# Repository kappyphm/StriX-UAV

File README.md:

# Small Fixed-Wing UAV Project

## Overview
This repository contains the design, control circuitry, firmware, and hardware assembly instructions for a small fixed-wing Unmanned Aerial Vehicle (UAV). The UAV supports remote control operation with a range of 500m–1km, automatic stabilization, GPS-based autonomous flight, and a return-to-home feature upon signal loss. The system is built around the STM32F103C8T6 microcontroller.

## Features
- **Remote Control**: 6 analog channels and 2 digital channels for precise control via an NRF24L01 module.
- **Flight Controller (FC)**:
  - Decodes control signals from NRF24L01 to manage 2 aileron servos, 1 rudder servo, 1 elevator servo, and 1 brushless motor ESC.
  - Reads UART signals from a GPS module for autonomous flight and return-to-home functionality.
  - Uses I2C IMU (ICM20948) for flight stabilization.
  - Supports firmware flashing and debugging via SWD.
  - Compatible with 2S–3S LiPo batteries, ensuring stable power delivery.
- **Flight Capabilities**:
  - Remote control with effective range of 500m–1km.
  - Automatic stabilization for smooth flight.
  - Autonomous flight via preloaded GPS waypoints.
  - Return-to-home feature on signal loss.

## Hardware Components
### Transmitter (TX) PCB
- **Function**: Captures 6 analog and 2 digital channels from user input.
- **Communication**: Transmits control signals via NRF24L01 module.

### Flight Controller (FC)
- **Microcontroller**: STM32F103C8T6.
- **Function**: Receives 6 PWM and 2 digital channels via NRF24L01.
- **Peripherals**:
  - 2 aileron servos, 1 rudder servo, 1 elevator servo.
  - 1 ESC for brushless motor control.
  - GPS module (UART) for navigation.
  - ICM20948 IMU (I2C) for stabilization.
- **Power**: Supports 2S–3S LiPo batteries with stable power regulation.
- **Debugging**: SWD interface for firmware updates and debugging.

## Contributing
Contributions are welcome! Please follow these steps:
1. Fork the repository.
2. Create a new branch (`git checkout -b feature/your-feature`).
3. Commit your changes (`git commit -m "Add your feature"`).
4. Push to the branch (`git push origin feature/your-feature`).
5. Open a pull request.

## License
This project is licensed under the MIT License. See the `LICENSE` file for details.

## Contact
For questions or suggestions, open an issue or contact [your email or GitHub handle].

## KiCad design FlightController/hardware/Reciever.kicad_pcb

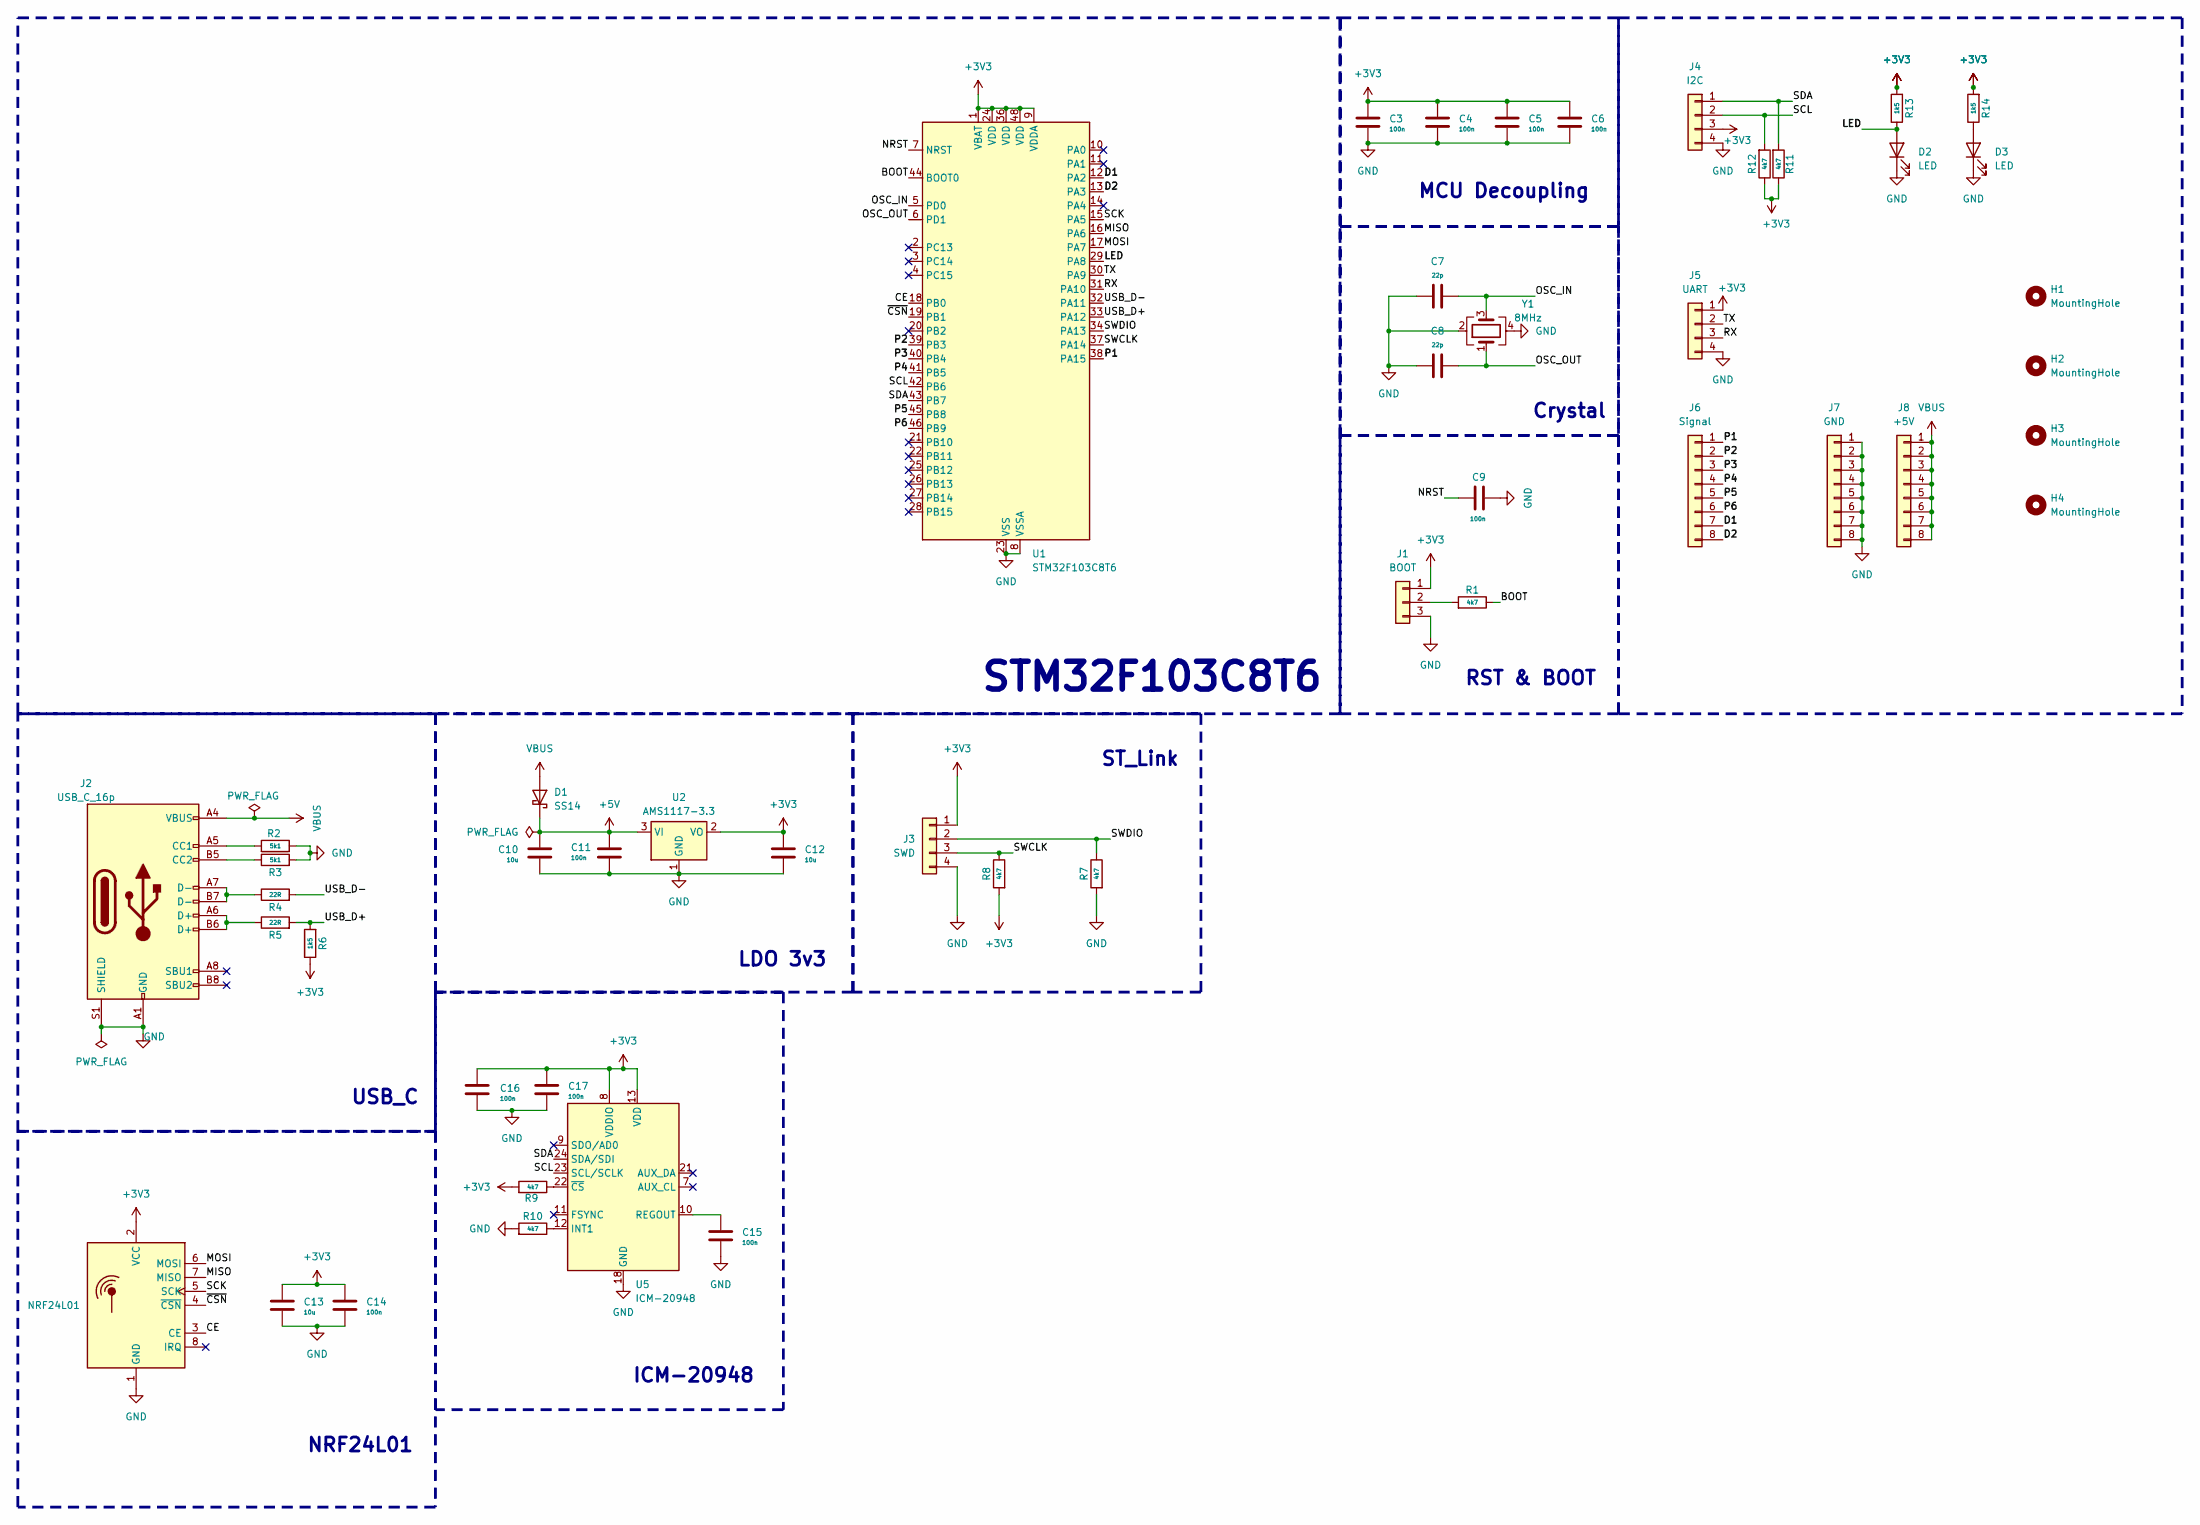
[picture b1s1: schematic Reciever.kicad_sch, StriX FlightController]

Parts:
C3, C4, C5, C6, C9, C11, C14, C15, C16, C17: 100n; C_0603_1608Metric
C7, C8: 22p; C_0603_1608Metric
C10, C12, C13: 10u; C_0603_1608Metric
D1: SS14; D_SMA
D2, D3: LED; LED_1206_3216Metric
H1, H2, H3, H4: MountingHole; MountingHole_2.5mm
J1: BOOT; PinHeader_1x03_P2.54mm_Vertical
J2: USB_C_16p; USB_C_Receptacle_HRO_TYPE-C-31-M-12
J3: SWD; PinHeader_1x04_P2.54mm_Vertical
J4: I2C; PinHeader_1x04_P2.54mm_Vertical
J5: UART; PinHeader_1x04_P2.54mm_Vertical
J6: Signal; PinHeader_1x08_P2.54mm_Vertical
J7: GND; PinHeader_1x08_P2.54mm_Vertical
J8: +5V; PinHeader_1x08_P2.54mm_Vertical
R1, R7, R8, R9, R10, R11, R12: 4k7; R_0603_1608Metric
R2, R3: 5k1; R_0603_1608Metric
R4, R5: 22R; R_0603_1608Metric
R6, R13, R14: 1k5; R_0603_1608Metric
U1: STM32F103C8T6; LQFP-48_7x7mm_P0.5mm
U2: AMS1117-3.3; SOT-223-3_TabPin2
U4: NRF24L01; NRF24L01_PA_LNA
U5: ICM-20948; InvenSense_QFN-24_3x3mm_P0.4mm
Y1: 8MHz; Crystal_SMD_5032-4Pin_5.0x3.2mm

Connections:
+3V3: C3.1, C4.1, C5.1, C6.1, C12.1, C13.1, C14.1, C16.1, C17.1, J1.1, J3.1, J4.3, J5.1, R6.1, R8.2, R9.2, R11.1, R12.1, R13.2, R14.2, U1.1 (VBAT), U1.9 (VDDA), U1.24 (VDD), U1.36 (VDD), U1.48 (VDD), U2.2 (VO), U4.2 (VCC), U5.8 (VDDIO), U5.13 (VDD)
+5V: C10.1, C11.1, D1.1 (K), U2.3 (VI)
/BOOT: R1.1, U1.44 (BOOT0)
/CE: U1.18 (PB0), U4.3 (CE)
/D1: J6.7, U1.12 (PA2)
/D2: J6.8, U1.13 (PA3)
/LED: D2.2 (A), R13.1, U1.29 (PA8)
/MISO: U1.16 (PA6), U4.7 (MISO)
/MOSI: U1.17 (PA7), U4.6 (MOSI)
/NRST: C9.1, U1.7 (NRST)
/OSC_IN: C7.2, U1.5 (PD0), Y1.3
/OSC_OUT: C8.2, U1.6 (PD1), Y1.1
/P1: J6.1, U1.38 (PA15)
/P2: J6.2, U1.39 (PB3)
/P3: J6.3, U1.40 (PB4)
/P4: J6.4, U1.41 (PB5)
/P5: J6.5, U1.45 (PB8)
/P6: J6.6, U1.46 (PB9)
/RX: J5.3, U1.31 (PA10)
/SCK: U1.15 (PA5), U4.5 (SCK)
/SCL: J4.2, R12.2, U1.42 (PB6), U5.23 (SCL/SCLK)
/SDA: J4.1, R11.2, U1.43 (PB7), U5.24 (SDA/SDI)
/SWCLK: J3.3, R8.1, U1.37 (PA14)
/SWDIO: J3.2, R7.1, U1.34 (PA13)
/TX: J5.2, U1.30 (PA9)
/USB_D+: R5.2, R6.2, U1.33 (PA12)
/USB_D-: R4.2, U1.32 (PA11)
/~CSN: U1.19 (PB1), U4.4 (~CSN)
GND: C3.2, C4.2, C5.2, C6.2, C7.1, C8.1, C9.2, C10.2, C11.2, C12.2, C13.2, C14.2, C15.2, C16.2, C17.2, D2.1 (K), D3.1 (K), J1.3, J2.A1 (GND), J2.A12 (GND), J2.B1 (GND), J2.B12 (GND), J2.S1 (SHIELD), J3.4, J4.4, J5.4, J7.1, J7.2, J7.3, J7.4, J7.5, J7.6, J7.7, J7.8, R2.2, R3.2, R7.2, R10.2, U1.8 (VSSA), U1.23 (VSS), U1.35 (VSS), U1.47 (VSS), U2.1 (GND), U4.1 (GND), U5.18 (GND), U5.20 (GND), Y1.2, Y1.4
unnamed: D3.2 (A), R14.1
unnamed: J1.2, R1.2
unnamed: J2.A5 (CC1), R2.1
unnamed: J2.B5 (CC2), R3.1
unnamed: J2.A6 (D+), J2.B6 (D+), R5.1
unnamed: J2.A7 (D-), J2.B7 (D-), R4.1
unnamed: R10.1, U5.12 (INT1)
unnamed: C15.1, U5.10 (REGOUT)
unnamed: R9.1, U5.22 (~CS)
VBUS: D1.2 (A), J2.A4 (VBUS), J2.A9 (VBUS), J2.B4 (VBUS), J2.B9 (VBUS), J8.1, J8.2, J8.3, J8.4, J8.5, J8.6, J8.7, J8.8

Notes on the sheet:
ST_Link
Crystal
LDO 3v3
USB_C
ICM-20948
RST & BOOT
NRF24L01
STM32F103C8T6
MCU Decoupling

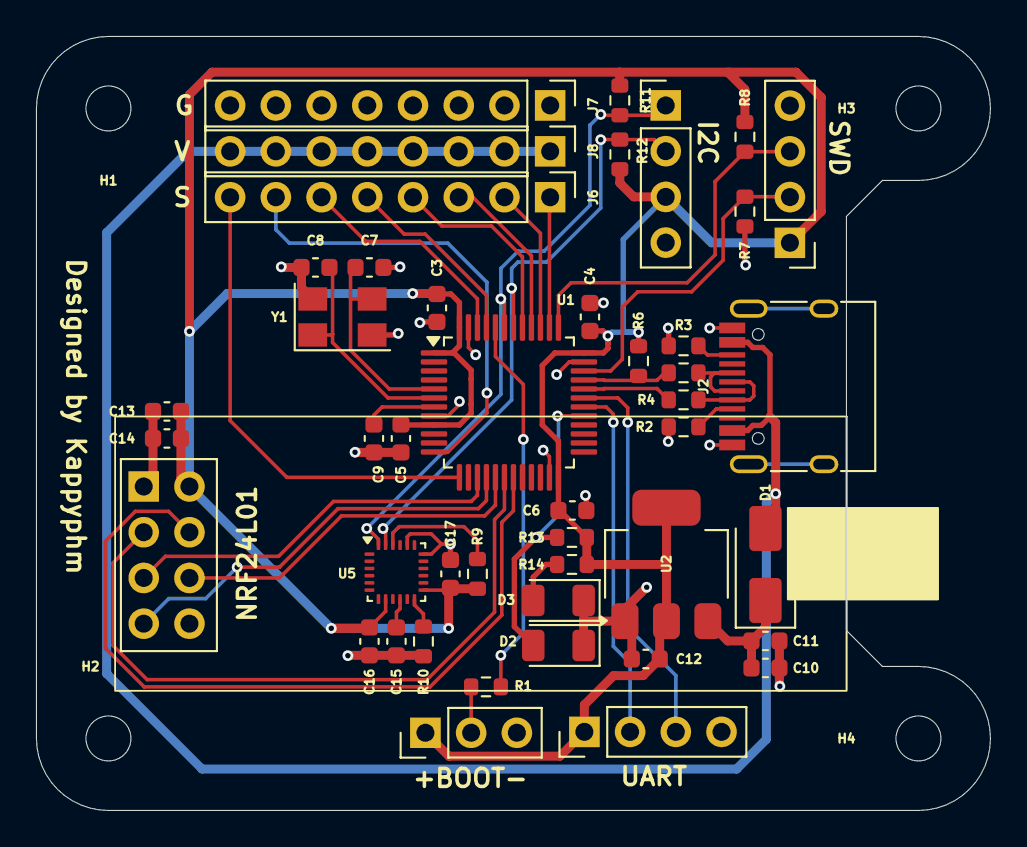
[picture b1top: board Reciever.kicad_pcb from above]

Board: 2 copper layers, 53.0 x 43.0 mm, 49 parts (0 on the bottom side), 39 nets.

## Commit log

2025-08-05 Init project
2025-08-05 ignore
2025-08-05 Update README with detailed project overview
    Expanded the README to include a comprehensive overview of the small fixed-wing UAV project, its features, hardware components, repository structure, setup instructions, requirements, contribution gu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
